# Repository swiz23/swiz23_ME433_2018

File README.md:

# swiz23_ME433_2018
Homework repo for the Advanced Mechatronics course at Northwestern University

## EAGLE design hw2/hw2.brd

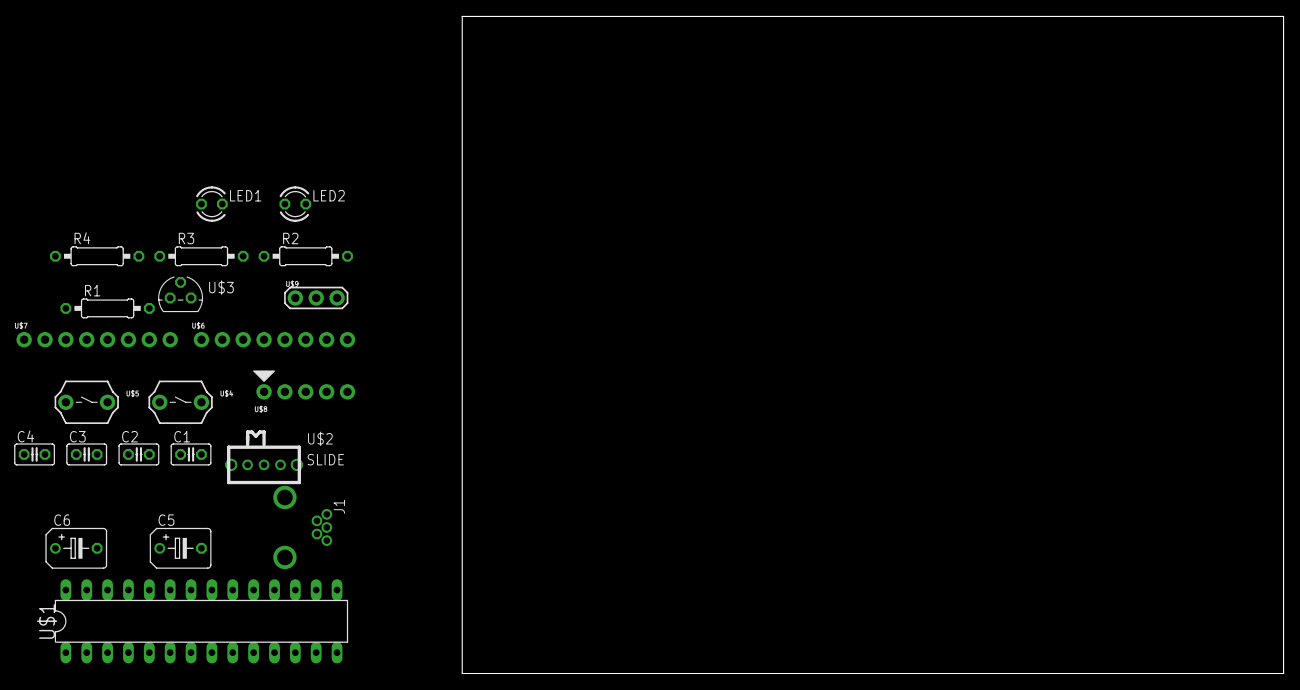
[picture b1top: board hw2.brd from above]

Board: 2 copper layers, 100.0 x 80.0 mm, 22 parts (0 on the bottom side), 27 nets, no tracks yet.

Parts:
C1, C2, C3, C4: 0.1uF; C025-025X050
C5, C6: 10uF; B45181B
J1: USB-MB-H
LED1: Red; LED3MM
LED2: Green; LED3MM
R1, R2: 330; 0207/10
R3, R4: 10k; 0207/10
U$1: PIC32MX250F128B; DIL28-3
U$2: SLIDE
U$3: MCP1702; TO92
U$4: RESET; PB
U$5: USER; PB
U$6, U$7: CONN_08; 1X08
U$8: PICKIT3; 1X05
U$9: 8MHz; OSC

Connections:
+3V3: C1.1, C2.1, C4.1, C6.+, LED1.A, R3.2, R4.2, U$1.13, U$1.23, U$1.28, U$3.3, U$7.2, U$8.2
+5V: C3.1, U$1.15, U$2.3, U$3.2, U$6.2
A0: U$1.2, U$7.8
A1: U$1.3, U$7.7
A4/LED: LED2.A, U$1.12, U$7.3
B2: U$1.6, U$7.6
B3: U$1.7, U$7.5
B4/USER: R4.1, U$1.11, U$5.1, U$7.4
B7: U$1.16, U$6.3
B8: U$1.17, U$6.4
B9: U$1.18, U$6.5
B13: U$1.24, U$6.6
B14: U$1.25, U$6.7
B15: U$1.26, U$6.8
D+: J1.D+, U$1.21
D-: J1.D-, U$1.22
GND: C1.2, C2.2, C3.2, C4.2, C5.-, C6.-, J1.GND, R1.1, R2.1, U$1.8, U$1.19, U$1.27, U$3.1, U$4.2, U$5.2, U$6.1, U$7.1, U$8.3, U$9.2
MCLR: R3.1, U$1.1, U$4.1, U$8.1
unnamed: J1.VBUS, U$2.2
unnamed: U$1.9, U$9.1
unnamed: U$1.10, U$9.3
unnamed: LED1.K, R1.2
unnamed: LED2.K, R2.2
unnamed: C5.+, U$1.20
PGC: U$1.5, U$8.5
PGD: U$1.4, U$8.4
USBID: J1.ID, U$1.14

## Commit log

2018-04-09 added pic showing voltage regulator with no cap or LED
2018-04-09 added pic showing clean 3.3V with all capacitors and LED
2018-04-09 completed circuit
2018-04-09 added circuit diagram
2018-04-09 created new project and pragma values and made green LED turn on
2018-04-10 completed final code
2018-04-10 last edit
2018-04-10 updated c code to fix a bug
2018-04-10 added some comments
2018-04-10 made a new movie
2018-04-10 fixed a comment
2018-04-11 voltage regulator, slide switch, usb connector devices made
2018-04-12 completed libraries
2018-04-12 added gitignore
2018-04-12 updated schematic
2018-04-12 completed schematic
2018-04-12 started board
2018-04-13 finished pcb layout
2018-04-15 completed layout and created zip file
2018-04-15 renamed zip file to gerber_files.zip
2018-04-15 renamed gerber zip file to 'swiz23_gerber_files.zip'
2018-04-19 completed how4
2018-04-20 completed working code for i2c
2018-04-22 optimized code
2018-04-22 added circuit schematic
2018-04-22 added demo video
2018-04-24 setup program skeleton
2018-04-24 complete code
2018-04-24 added answers to 'reference' questions at bottom of main.c file and added demo vid
2018-04-27 project with both lcd and IMU and IMU is reading data
2018-04-27 added axes and got acc values printing correctly
2018-04-29 finished code and added video
2018-05-01 almost finished harmony program for hw7
2018-05-01 completed program code
2018-05-04 completed hw9
2018-05-04 final edits
2018-05-04 removed lcd stuff
2018-05-09 skeleton for hw10 completed
2018-05-09 got hw9 to work with LCD
2018-05-09 added axes for accel when r is not pressed. when r is pressed, nothing is printed out to lcd since otherwise, code runs at less than 100Hz
2018-05-09 finished maf filter
2018-05-10 completed project without pdf
2018-05-10 added pdf explaining filter choices and which one is better
2018-05-10 set up skeleton for hw11 with all neccessary files
2018-05-10 completed hw11
2018-05-15 completed hw12
2018-05-17 partially completed hw13
2018-05-17 completed hw13
2018-05-22 completed hw14
2018-05-29 completed hw15
2018-06-13 some of hw17 and hw18
2018-06-13 pi controller
2018-06-13 done with hw16
2018-06-13 completed android code for hw18
2018-06-13 completed tuned pi of 'bot
2018-06-13 uploaded hw17
2018-06-13 finished hw18 - added pics
